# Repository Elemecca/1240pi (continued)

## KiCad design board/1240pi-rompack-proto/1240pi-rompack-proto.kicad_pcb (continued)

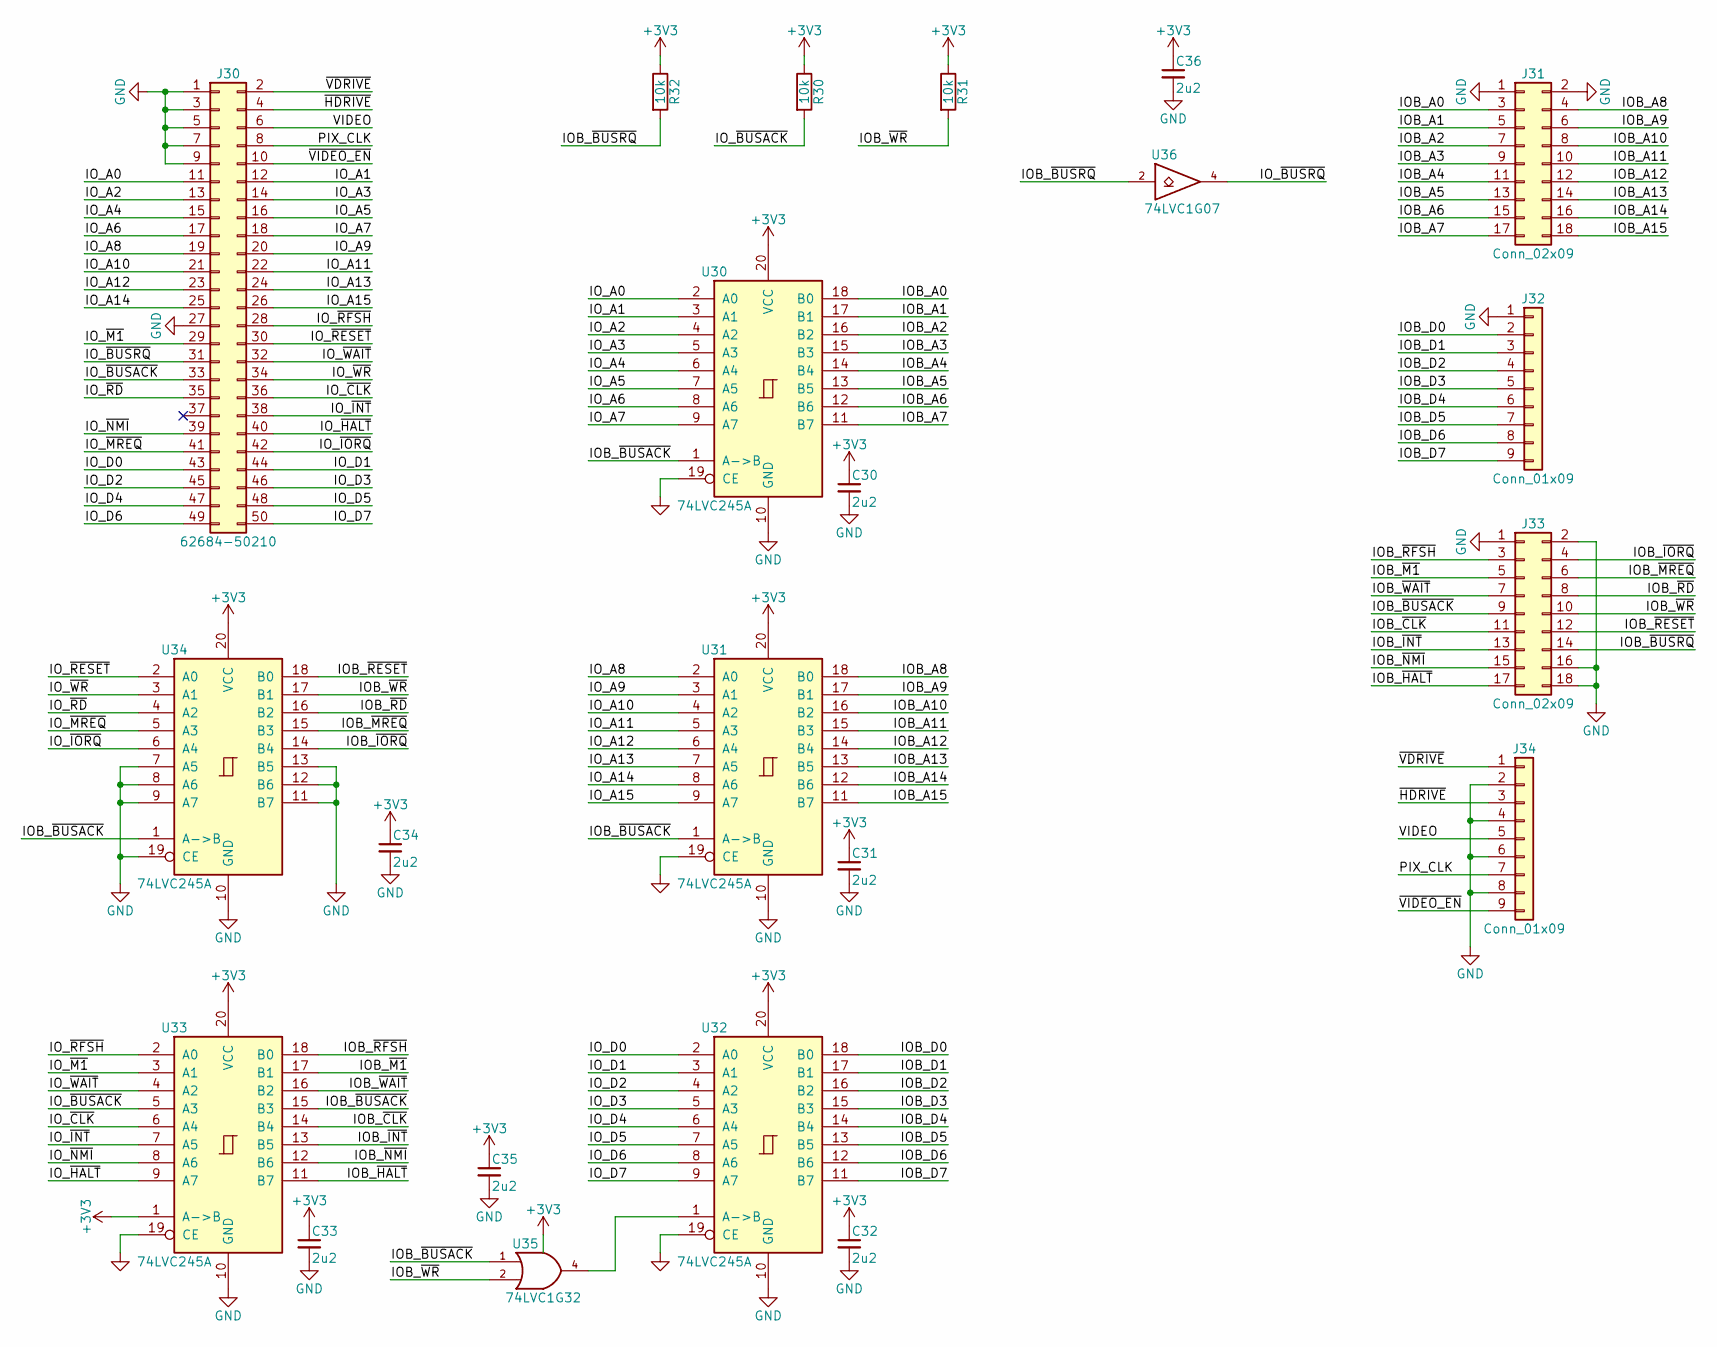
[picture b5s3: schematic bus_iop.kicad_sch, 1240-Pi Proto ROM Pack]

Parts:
C30, C31, C32, C33, C34, C35, C36: 2u2; C_0603_1608Metric
J30: 62684-50210; Amphenol_62684-50210
J31, J33: Conn_02x09; PinHeader_2x09_P2.54mm_Vertical
J32, J34: Conn_01x09; PinHeader_1x09_P2.54mm_Vertical
R30, R31, R32: 10k; R_0603_1608Metric
U30, U31, U32, U33, U34: 74LVC245A; TSSOP-20_4.4x6.5mm_P0.65mm
U35: 74LVC1G32; SOT-353_SC-70-5
U36: 74LVC1G07; Package_SC-74A

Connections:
+3V3: C30.1, C31.1, C32.1, C33.1, C34.1, C35.1, C36.1, R30.1, R31.1, R32.1, U30.20 (VCC), U31.20 (VCC), U32.20 (VCC), U33.1 (A->B), U33.20 (VCC), U34.20 (VCC), U35.5 (VCC), U36.5 (VCC); also elsewhere on the board
/IO Proc Bus/IOB_A0: J31.3, U30.18 (B0)
/IO Proc Bus/IOB_A1: J31.5, U30.17 (B1)
/IO Proc Bus/IOB_A2: J31.7, U30.16 (B2)
/IO Proc Bus/IOB_A3: J31.9, U30.15 (B3)
/IO Proc Bus/IOB_A4: J31.11, U30.14 (B4)
/IO Proc Bus/IOB_A5: J31.13, U30.13 (B5)
/IO Proc Bus/IOB_A6: J31.15, U30.12 (B6)
/IO Proc Bus/IOB_A7: J31.17, U30.11 (B7)
/IO Proc Bus/IOB_A8: J31.4, U31.18 (B0)
/IO Proc Bus/IOB_A9: J31.6, U31.17 (B1)
/IO Proc Bus/IOB_A10: J31.8, U31.16 (B2)
/IO Proc Bus/IOB_A11: J31.10, U31.15 (B3)
/IO Proc Bus/IOB_A12: J31.12, U31.14 (B4)
/IO Proc Bus/IOB_A13: J31.14, U31.13 (B5)
/IO Proc Bus/IOB_A14: J31.16, U31.12 (B6)
/IO Proc Bus/IOB_A15: J31.18, U31.11 (B7)
/IO Proc Bus/IOB_D0: J32.2, U32.18 (B0)
/IO Proc Bus/IOB_D1: J32.3, U32.17 (B1)
/IO Proc Bus/IOB_D2: J32.4, U32.16 (B2)
/IO Proc Bus/IOB_D3: J32.5, U32.15 (B3)
/IO Proc Bus/IOB_D4: J32.6, U32.14 (B4)
/IO Proc Bus/IOB_D5: J32.7, U32.13 (B5)
/IO Proc Bus/IOB_D6: J32.8, U32.12 (B6)
/IO Proc Bus/IOB_D7: J32.9, U32.11 (B7)
/IO Proc Bus/IOB_~BUSACK: J33.9, U30.1 (A->B), U31.1 (A->B), U33.15 (B3), U34.1 (A->B), U35.1
/IO Proc Bus/IOB_~BUSRQ: J33.14, R32.2, U36.2
/IO Proc Bus/IOB_~CLK: J33.11, U33.14 (B4)
/IO Proc Bus/IOB_~HALT: J33.17, U33.11 (B7)
/IO Proc Bus/IOB_~INT: J33.13, U33.13 (B5)
/IO Proc Bus/IOB_~IORQ: J33.4, U34.14 (B4)
/IO Proc Bus/IOB_~M1: J33.5, U33.17 (B1)
/IO Proc Bus/IOB_~MREQ: J33.6, U34.15 (B3)
/IO Proc Bus/IOB_~NMI: J33.15, U33.12 (B6)
/IO Proc Bus/IOB_~RD: J33.8, U34.16 (B2)
/IO Proc Bus/IOB_~RESET: J33.12, U34.18 (B0)
/IO Proc Bus/IOB_~RFSH: J33.3, U33.18 (B0)
/IO Proc Bus/IOB_~WAIT: J33.7, U33.16 (B2)
/IO Proc Bus/IOB_~WR: J33.10, R31.2, U34.17 (B1), U35.2
/IO Proc Bus/IO_A0: J30.11, U30.2 (A0)
/IO Proc Bus/IO_A1: J30.12, U30.3 (A1)
/IO Proc Bus/IO_A2: J30.13, U30.4 (A2)
/IO Proc Bus/IO_A3: J30.14, U30.5 (A3)
/IO Proc Bus/IO_A4: J30.15, U30.6 (A4)
/IO Proc Bus/IO_A5: J30.16, U30.7 (A5)
/IO Proc Bus/IO_A6: J30.17, U30.8 (A6)
/IO Proc Bus/IO_A7: J30.18, U30.9 (A7)
/IO Proc Bus/IO_A8: J30.19, U31.2 (A0)
/IO Proc Bus/IO_A9: J30.20, U31.3 (A1)
/IO Proc Bus/IO_A10: J30.21, U31.4 (A2)
/IO Proc Bus/IO_A11: J30.22, U31.5 (A3)
/IO Proc Bus/IO_A12: J30.23, U31.6 (A4)
/IO Proc Bus/IO_A13: J30.24, U31.7 (A5)
/IO Proc Bus/IO_A14: J30.25, U31.8 (A6)
/IO Proc Bus/IO_A15: J30.26, U31.9 (A7)
/IO Proc Bus/IO_D0: J30.43, U32.2 (A0)
/IO Proc Bus/IO_D1: J30.44, U32.3 (A1)
/IO Proc Bus/IO_D2: J30.45, U32.4 (A2)
/IO Proc Bus/IO_D3: J30.46, U32.5 (A3)
/IO Proc Bus/IO_D4: J30.47, U32.6 (A4)
/IO Proc Bus/IO_D5: J30.48, U32.7 (A5)
/IO Proc Bus/IO_D6: J30.49, U32.8 (A6)
/IO Proc Bus/IO_D7: J30.50, U32.9 (A7)
/IO Proc Bus/IO_~BUSACK: J30.33, R30.2, U33.5 (A3)
/IO Proc Bus/IO_~BUSRQ: J30.31, U36.4
/IO Proc Bus/IO_~CLK: J30.36, U33.6 (A4)
/IO Proc Bus/IO_~HALT: J30.40, U33.9 (A7)
/IO Proc Bus/IO_~INT: J30.38, U33.7 (A5)
/IO Proc Bus/IO_~IORQ: J30.42, U34.6 (A4)
/IO Proc Bus/IO_~M1: J30.29, U33.3 (A1)
/IO Proc Bus/IO_~MREQ: J30.41, U34.5 (A3)
/IO Proc Bus/IO_~NMI: J30.39, U33.8 (A6)
/IO Proc Bus/IO_~RD: J30.35, U34.4 (A2)
/IO Proc Bus/IO_~RESET: J30.30, U34.2 (A0)
/IO Proc Bus/IO_~RFSH: J30.28, U33.2 (A0)
/IO Proc Bus/IO_~WAIT: J30.32, U33.4 (A2)
/IO Proc Bus/IO_~WR: J30.34, U34.3 (A1)
/IO Proc Bus/PIX_CLK: J30.8, J34.7
/IO Proc Bus/VIDEO: J30.6, J34.5
/IO Proc Bus/~HDRIVE: J30.4, J34.3
/IO Proc Bus/~VDRIVE: J30.2, J34.1
/IO Proc Bus/~VIDEO_EN: J30.10, J34.9
unnamed: U32.1 (A->B), U35.4

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
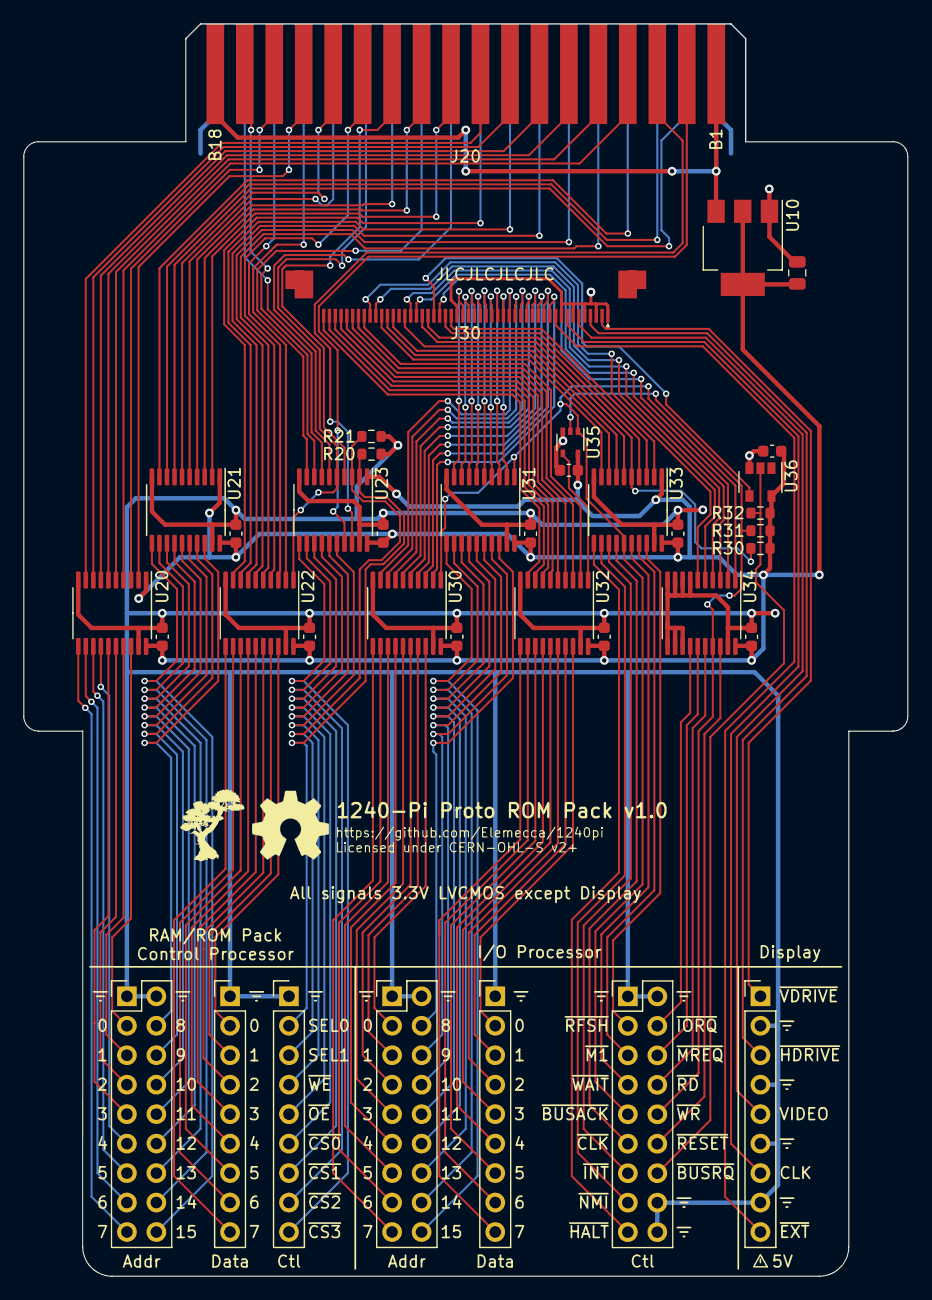
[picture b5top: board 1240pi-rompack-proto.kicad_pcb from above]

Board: 2 copper layers, 76.2 x 108.0 mm, 38 parts (1 on the bottom side), 149 nets.

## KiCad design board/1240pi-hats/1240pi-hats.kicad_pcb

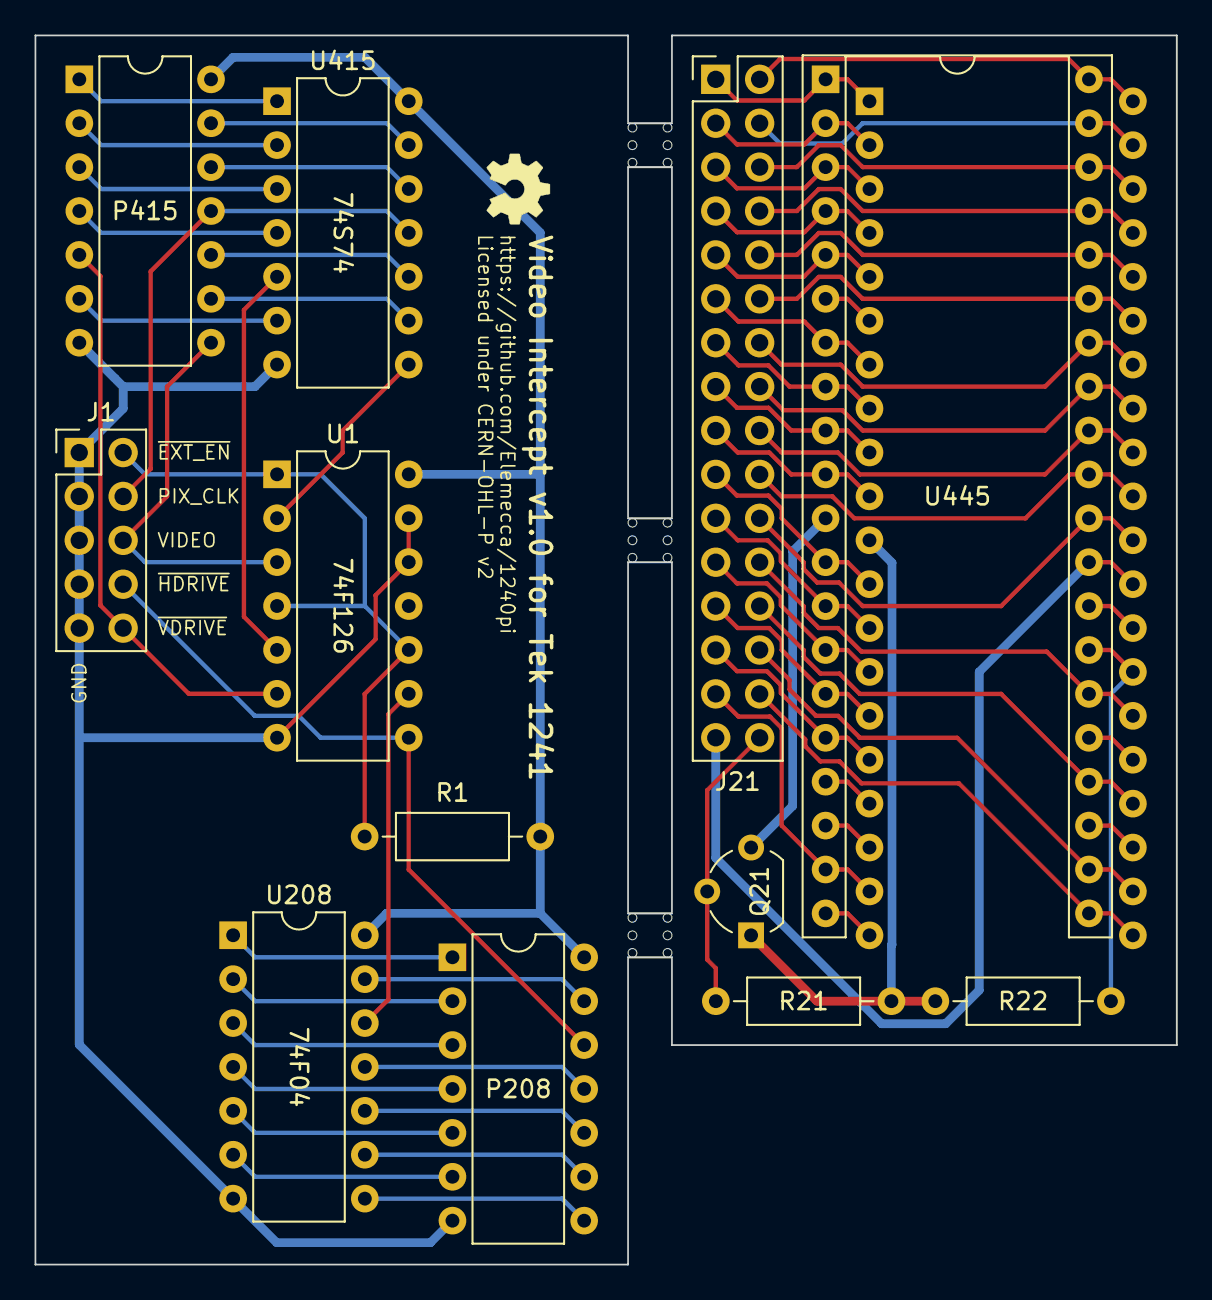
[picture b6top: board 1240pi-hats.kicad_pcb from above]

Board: 2 copper layers, 66.0 x 71.1 mm, 14 parts (0 on the bottom side), 70 nets.

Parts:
J1: Conn_02x05_Odd_Even; PinHeader_2x05_P2.54mm_Vertical
J21: Conn_02x16_Odd_Even; PinHeader_2x16_P2.54mm_Vertical
OSHW: LOGO; OSHW
P208, P415: Header; DIP-14_W7.62mm
P445: Header; DIP-40_W15.24mm
Q21: Q_PMOS_SGD; TO-92_Wide
R1: 4k7; R_Axial_DIN0207_L6.3mm_D2.5mm_P10.16mm_Horizontal
R21, R22: 10k; R_Axial_DIN0207_L6.3mm_D2.5mm_P10.16mm_Horizontal
U1: 74F126; DIP-14_W7.62mm
U208: 74F04; DIP-14_W7.62mm
U415: 74S74; DIP-14_W7.62mm
U445: Z80; DIP-40_W15.24mm_Socket

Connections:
+5V: P208.14 (VCC), P415.14 (VCC), P445.11 (VCC), Q21.1 (S), R1.1, R21.1, R22.1, U1.14 (VCC), U208.14 (VCC), U415.14 (VCC)
/Display/PIX_CLK: J1.4, P415.11 (C), U415.11 (C)
/Display/VIDEO: J1.6, P415.8 (~Q), U1.3
/Display/~EXT_EN: J1.2, R1.2, U1.1, U1.4, U1.10
/Display/~HDRIVE: J1.8, P208.12, U1.8
/Display/~VDRIVE: J1.10, P415.5 (Q), U1.6
/IO Processor/A0: J21.22, P445.30 (A0), U445.30 (A0)
/IO Processor/A1: J21.20, P445.31 (A1), U445.31 (A1)
/IO Processor/A2: J21.18, P445.32 (A2), U445.32 (A2)
/IO Processor/A3: J21.16, P445.33 (A3), U445.33 (A3)
/IO Processor/A4: J21.14, P445.34 (A4), U445.34 (A4)
/IO Processor/A5: J21.12, P445.35 (A5), U445.35 (A5)
/IO Processor/A6: J21.10, P445.36 (A6), U445.36 (A6)
/IO Processor/A7: J21.8, P445.37 (A7), U445.37 (A7)
/IO Processor/A8: J21.6, P445.38 (A8), U445.38 (A8)
/IO Processor/A9: J21.4, P445.39 (A9), U445.39 (A9)
/IO Processor/A10: J21.2, P445.40 (A10), U445.40 (A10)
/IO Processor/A11: J21.1, P445.1 (A11), U445.1 (A11)
/IO Processor/A12: J21.3, P445.2 (A12), U445.2 (A12)
/IO Processor/A13: J21.5, P445.3 (A13), U445.3 (A13)
/IO Processor/A14: J21.7, P445.4 (A14), U445.4 (A14)
/IO Processor/A15: J21.9, P445.5 (A15), U445.5 (A15)
/IO Processor/D0: J21.23, P445.14 (D0), U445.14 (D0)
/IO Processor/D1: J21.25, P445.15 (D1), U445.15 (D1)
/IO Processor/D2: J21.19, P445.12 (D2), U445.12 (D2)
/IO Processor/D3: J21.13, P445.8 (D3), U445.8 (D3)
/IO Processor/D4: J21.11, P445.7 (D4), U445.7 (D4)
/IO Processor/D5: J21.15, P445.9 (D5), U445.9 (D5)
/IO Processor/D6: J21.17, P445.10 (D6), U445.10 (D6)
/IO Processor/D7: J21.21, P445.13 (D7), U445.13 (D7)
/IO Processor/~BUSACK: P445.23 (~BUSACK), U445.23 (~BUSACK)
/IO Processor/~BUSRQ: P445.25 (~BUSRQ), U445.25 (~BUSRQ)
/IO Processor/~CLK: P445.6 (~CLK), U445.6 (~CLK)
/IO Processor/~HALT: P445.18 (~HALT), U445.18 (~HALT)
/IO Processor/~INT: J21.27, P445.16 (~INT), U445.16 (~INT)
/IO Processor/~IORQ: P445.20 (~IORQ), U445.20 (~IORQ)
/IO Processor/~M1: P445.27 (~M1), R22.2, U445.27 (~M1)
/IO Processor/~MREQ: J21.29, P445.19 (~MREQ), U445.19 (~MREQ)
/IO Processor/~NMI: P445.17 (~NMI), U445.17 (~NMI)
/IO Processor/~RD: J21.30, P445.21 (~RD), U445.21 (~RD)
/IO Processor/~RESET: J21.24, P445.26 (~RESET), U445.26 (~RESET)
/IO Processor/~RFSH: P445.28 (~RFSH), U445.28 (~RFSH)
/IO Processor/~WAIT: J21.26, P445.24 (~WAIT), U445.24 (~WAIT)
/IO Processor/~WR: J21.28, P445.22 (~WR), U445.22 (~WR)
/IO Processor/~Z80_EN: J21.32, Q21.2 (G), R21.2
GND: J1.1, J1.3, J1.5, J1.7, J1.9, J21.31, P208.7 (GND), P415.7 (GND), P445.29 (GND), U1.7 (GND), U1.12, U1.13, U208.7 (GND), U415.7 (GND), U445.29 (GND)
unnamed: U1.9, U208.12
unnamed: P208.1, U208.1
unnamed: P208.2, U208.2
unnamed: P208.3, U208.3
unnamed: P208.4, U208.4
unnamed: P208.5, U208.5
unnamed: P208.6, U208.6
unnamed: P208.8, U208.8
unnamed: P208.9, U208.9
unnamed: P208.10, U208.10
unnamed: P208.11, U208.11
unnamed: P208.13, U208.13
unnamed: P415.1 (~R), U415.1 (~R)
unnamed: P415.2 (D), U415.2 (D)
unnamed: P415.3 (C), U415.3 (C)
unnamed: P415.4 (~S), U415.4 (~S)
unnamed: U1.5, U415.5 (Q)
unnamed: P415.6 (~Q), U415.6 (~Q)
unnamed: U1.2, U415.8 (~Q)
unnamed: P415.9 (Q), U415.9 (Q)
unnamed: P415.10 (~S), U415.10 (~S)
unnamed: P415.12 (D), U415.12 (D)
unnamed: P415.13 (~R), U415.13 (~R)
unnamed: Q21.3 (D), U445.11 (VCC)

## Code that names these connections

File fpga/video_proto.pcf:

set_io clk_pixel C8

set_io video B7
set_io hdrive C7
set_io vdrive_green A7

set_io pixel[0] C14
set_io pixel[1] B15
set_io pixel[2] D13
set_io pixel[3] B14
set_io pixel[4] C12
set_io pixel[5] E11
set_io pixel[6] C13
set_io pixel[7] A16

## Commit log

2022-04-13 Start with 1240 plug-in card outline.
2022-04-16 Start modelling display board in logisim.
2022-04-16 Finish copying page 48 into logisim.
2022-04-16 Build page 49 in logisim.
2022-04-16 Build page 50 in logisim.
2022-04-16 Fix PAL IO direction and re-dump image.
2022-04-18 Play with more board form-factor options.
2022-04-18 Start building video out in FPGA.
2022-04-20 Start playing with display hats.
2022-04-21 Redesign display hat to use a single board.
2022-04-21 Finish up display hat board.
2022-04-21 Add IO Processor hat board.
2022-04-22 Add tabs to hats board.
2022-04-22 Split hats into separate projects / boards.
2022-04-22 Add hat boards to Aisler.
2022-04-22 Route HDMI in resistor networks.
2022-04-22 Remove extraneous LVDS termination resistors.
2022-04-22 Add labels to HDMI board.
2022-04-23 Add and route non-TMDS lines for sink port.
2022-04-23 Connect source port hotplug detect.
2022-04-24 Tweak sikscreen.
2022-04-27 Set up most of the non-TMDS source stuff.
2022-05-15 Tweak HDMI bits.
2022-05-21 Switch hat boards from IDC ribbons to flat flex cables.
2022-05-21 Update board license to CERN-OHL-S v2+.
2022-05-21 Remove full-size IO Processor replacement board.
2022-05-24 Start ROM pack proto board.
2022-05-26 Fully route IO processor lines.
2022-05-26 Drop proto ROM pack to 2 layers.
2022-05-27 Route in edge connector.
2022-05-27 Add 3.3v regulator.
2022-05-27 Move around A8..15 vias.
2022-05-27 Add voltage labels.
2022-05-27 Disconnect and pull up Z80 pins not used by the 1240.
2022-05-27 Fix names of BUSRQ and IORQ nets.
2022-06-26 Add bonsai logo to boards.
2022-06-27 Fix DRC issues on HDMI board.
2022-06-27 Deskew HDMI Proto sink lines.
2022-06-28 Connect HDMI Proto output differential lines.
2022-06-28 Export boards for manufacturing.
2022-07-16 Rotate sockets on hat boards 180 to match actual orientation.
2022-07-21 Use correct pin of U208 in display hay.
2022-08-05 Fix 1G17QDRY pinout.
2022-08-11 Add trivial Makefile for builds with Project Icestorm.
2022-08-11 Audit and correct Logisim display board against schematic.
2022-08-12 Working three-color test pattern.
2022-08-12 Add a bunch of probes to logisim schematic.
2022-08-18 Add laser-cuttable breakout labels for Olimex dev board.
2022-08-20 Update pinout for Olimex dev board.
2022-08-20 Add offset between hsync and horizontal blanking.
2022-08-20 Remove debugging clock outputs.
2022-08-21 Fix tab size on breakout labels, add printable version.
2022-08-26 Add pixel-counter output to make a gradient.
2022-09-29 Add more stuff to rompack board.
2022-10-31 Add buffers to card-edge connector.
2022-11-01 Split connectors out of CM4 footprint.
2022-11-03 Route HDMI output port.
2022-11-03 Add footprint for USB daughter board connector.
2022-11-04 Rearrange IO Proc hat, add IO Proc interface.
2022-11-05 Add description to IO proc interface.
2022-12-03 Reroute IO Proc hat again and add buffers on rompack board.
2022-12-04 Convert display board hat to 3v3.
